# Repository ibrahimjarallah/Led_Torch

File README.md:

# LED Torch — CR2032 Coin Cell PCB

> A compact, battery-powered LED torch circuit built around a CR2032 coin cell.  
> Minimal BOM, DPST tactile switch control, and a current-limited 5mm LED.  
> Designed and laid out in **KiCad 9.0** — schematic + 2-layer PCB with full fabrication outputs.

---

## 📸 3D Views

| Front | Back |
|:---:|:---:|
|  |  |

## 🖼️ PCB Layout (2D)

| Front | Back |
|:---:|:---:|
|  |  |

## 🟤 PCB Layout — Copper Fill (2D)

| Front | Back |
|:---:|:---:|
|  |  |

## 📐 Schematic

---

## ⚡ Specifications

| Parameter            | Value                            |
|----------------------|----------------------------------|
| Supply Voltage       | 3V DC (CR2032 coin cell)         |
| LED Forward Voltage  | ~2V (typical 5mm LED)            |
| Current Limit        | ~10mA (R1 = 100Ω)               |
| Switch               | DPST tactile (Omron B3F series)  |
| PCB Layers           | 2                                |
| Designed With        | KiCad 9.0.7                      |

---

## 🔧 How It Works

### 1. Power Source
A **CR2032 coin cell** (BT1) provides **3V DC**. The Keystone 1058 holder allows easy battery replacement.

### 2. Switch Control
**SW1** is an **Omron B3F DPST tactile switch** wired to connect/disconnect the circuit.  
Pressing SW1 completes the circuit and powers the LED.

### 3. Current Limiting
**R1 (100Ω)** limits the LED current to a safe level:

```
I = (Vbat - Vf) / R1 = (3V - 2V) / 100Ω ≈ 10mA
```

This keeps the CR2032 within its continuous discharge rating while delivering adequate brightness.

### 4. LED Output
**D1** is a standard **5mm through-hole LED** — visible indicator/torch output.

---

## 📦 Bill of Materials

| ID | Designator | Description | Quantity | Footprint |
|----|------------|-------------|----------|-----------|
| 1 | BT1 | CR2032 Coin Cell Battery Holder | 1 | Keystone 1058 1×CR2032 |
| 2 | D1 | LED 5mm | 1 | LED_D5.0mm |
| 3 | R1 | Resistor 100Ω | 1 | Axial DIN0204 L3.6mm P7.62mm |
| 4 | SW1 | Tactile Switch DPST (Omron B3F) | 1 | SW_TH_Tactile_Omron_B3F-100x |

---

## 📁 Repository Structure

```
Led_Torch/
├── Led_Torch.kicad_pro          # KiCad project file
├── Led_Torch.kicad_sch          # Schematic
├── Led_Torch.kicad_pcb          # PCB layout
├── Led_Torch.xml                # KiCad XML component data
├── BOM/
│   └── Led_Torch.csv            # Bill of materials
├── Netlist/
│   └── Led_Torch.net            # Netlist
├── Gerbers+drills/              # Fabrication Gerber + drill files
│   ├── Led_Torch-F_Cu.gbr
│   ├── Led_Torch-B_Cu.gbr
│   ├── Led_Torch-F_Mask.gbr
│   ├── Led_Torch-B_Mask.gbr
│   ├── Led_Torch-F_Silkscreen.gbr
│   ├── Led_Torch-B_Silkscreen.gbr
│   ├── Led_Torch-F_Paste.gbr
│   ├── Led_Torch-B_Paste.gbr
│   ├── Led_Torch-F_Fab.gbr
│   ├── Led_Torch-B_Fab.gbr
│   ├── Led_Torch-Edge_Cuts.gbr
│   ├── Led_Torch-PTH-drl.gbr
│   ├── Led_Torch-NPTH-drl.gbr
│   └── Led_Torch-job.gbrjob
├── drills/                      # Drill files (if separate)
├── 2d_view/
│   ├── 2d_view_Front.png
│   └── 2d_view_Back.png
├── 3d_view/
│   ├── 3d_view_front.png
│   └── 3d_view_back.png
├── Schematic_view/
│   ├── schematic_view.png
│   └── Led_Torch.pdf
├── pdf_assembly/
│   ├── Led_Torch-F_Cu.pdf
│   ├── Led_Torch-F_Fab.pdf
│   └── Led_Torch-F_Silkscreen.pdf
└── STEP_3d/
    └── Led_Torch.step           # 3D STEP model for mechanical integration
```

---

## 🖥️ Opening the Project

1. Install [KiCad 9.0+](https://www.kicad.org/download/)
2. Clone this repository:
   ```bash
   git clone https://github.com/ibrahimjarallah/Led_Torch.git
   ```
3. Open `Led_Torch.kicad_pro` in KiCad

---

## 🏭 Fabrication

All fabrication outputs are ready in the `Gerbers+drills/` folder.  
Compatible with standard PCB manufacturers (JLCPCB, PCBWay, OSHPark, etc.).

- Load `Led_Torch-job.gbrjob` directly into any Gerber viewer or fab upload portal
- PTH and NPTH drill files provided in Gerber format

---

## 🧩 3D Model

A **STEP file** is available in `STEP_3d/Led_Torch.step` for mechanical enclosure design and CAD integration (SolidWorks, FreeCAD, Fusion 360, etc.).

---

## ⚠️ Notes

- CR2032 typical capacity: ~220mAh → at 10mA continuous, runtime ≈ **22 hours**
- For longer battery life, reduce R1 to 220Ω (≈4.5mA) or add a PWM dimmer stage
- LED polarity must be observed during assembly — anode to R1, cathode to GND

---

## 📄 License

This project is licensed under the **MIT License**.  
You are free to use, modify, and distribute it with attribution.

---

## 👤 Author

**Ibrahim Jarallah**  
GitHub: [ibrahimjarallah](https://github.com/ibrahimjarallah) \
LinkedIn: [ibrahimjarallah](https://www.linkedin.com/in/ibrahim-jarallah)

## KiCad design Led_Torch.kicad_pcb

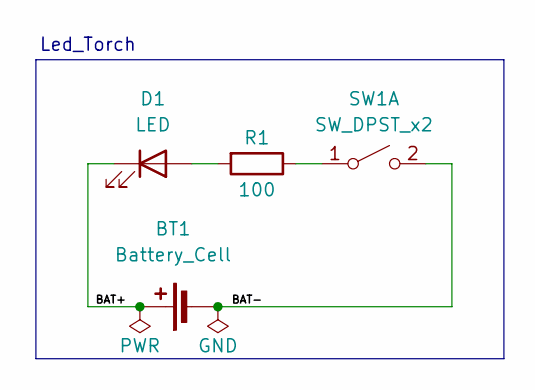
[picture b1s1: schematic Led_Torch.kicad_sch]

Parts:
BT1: Battery_Cell; BatteryHolder_Keystone_1058_1x2032
D1: LED; LED_D5.0mm
R1: 100; R_Axial_DIN0204_L3.6mm_D1.6mm_P7.62mm_Horizontal
SW1: SW_DPST_x2; SW_TH_Tactile_Omron_B3F-100x

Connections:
/BAT+: BT1.1 (+), D1.1 (K)
/BAT-: BT1.2 (-), SW1.2 (B)
unnamed: D1.2 (A), R1.2
unnamed: R1.1, SW1.1 (A)

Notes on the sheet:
Led_Torch

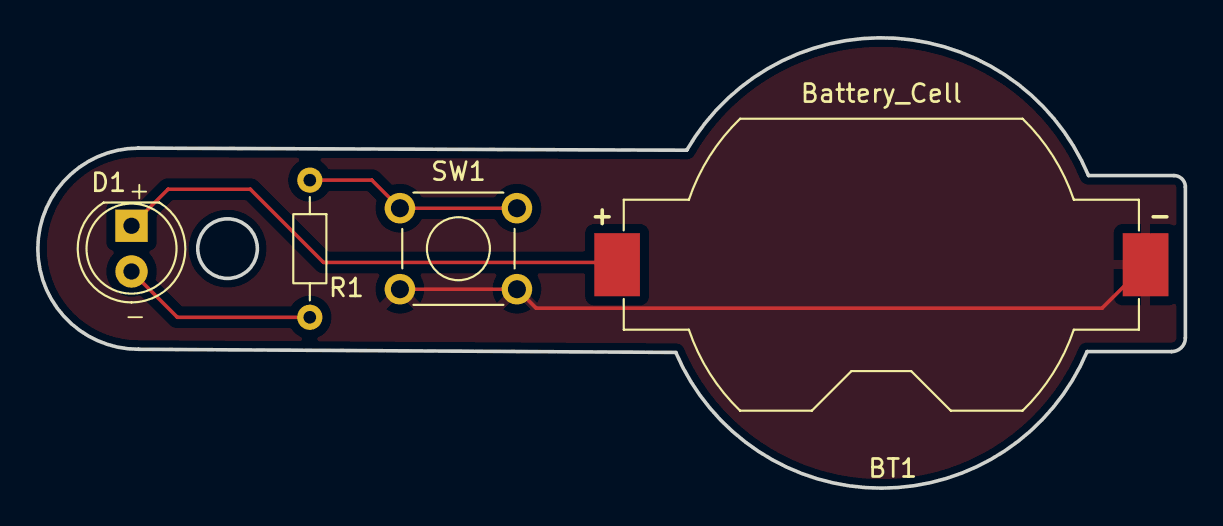
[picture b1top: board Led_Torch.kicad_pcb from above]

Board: 2 copper layers, 63.8 x 25.0 mm, 4 parts (0 on the bottom side), 4 nets.

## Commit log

2026-03-09 Initial commit: CR2032 LED torch — schematic, PCB layout, Gerbers, BOM, netlist, 2D/3D views, STEP model, assembly PDFs
2026-03-09 updated personal info
2026-03-09 Update: revised schematic/PCB layout, regenerated Gerbers/STEP/views, added copper fill 2D views, fixed company name
2026-03-09 updated some info
2026-03-09 updated schmatic view
2026-03-09 updated pcb views
